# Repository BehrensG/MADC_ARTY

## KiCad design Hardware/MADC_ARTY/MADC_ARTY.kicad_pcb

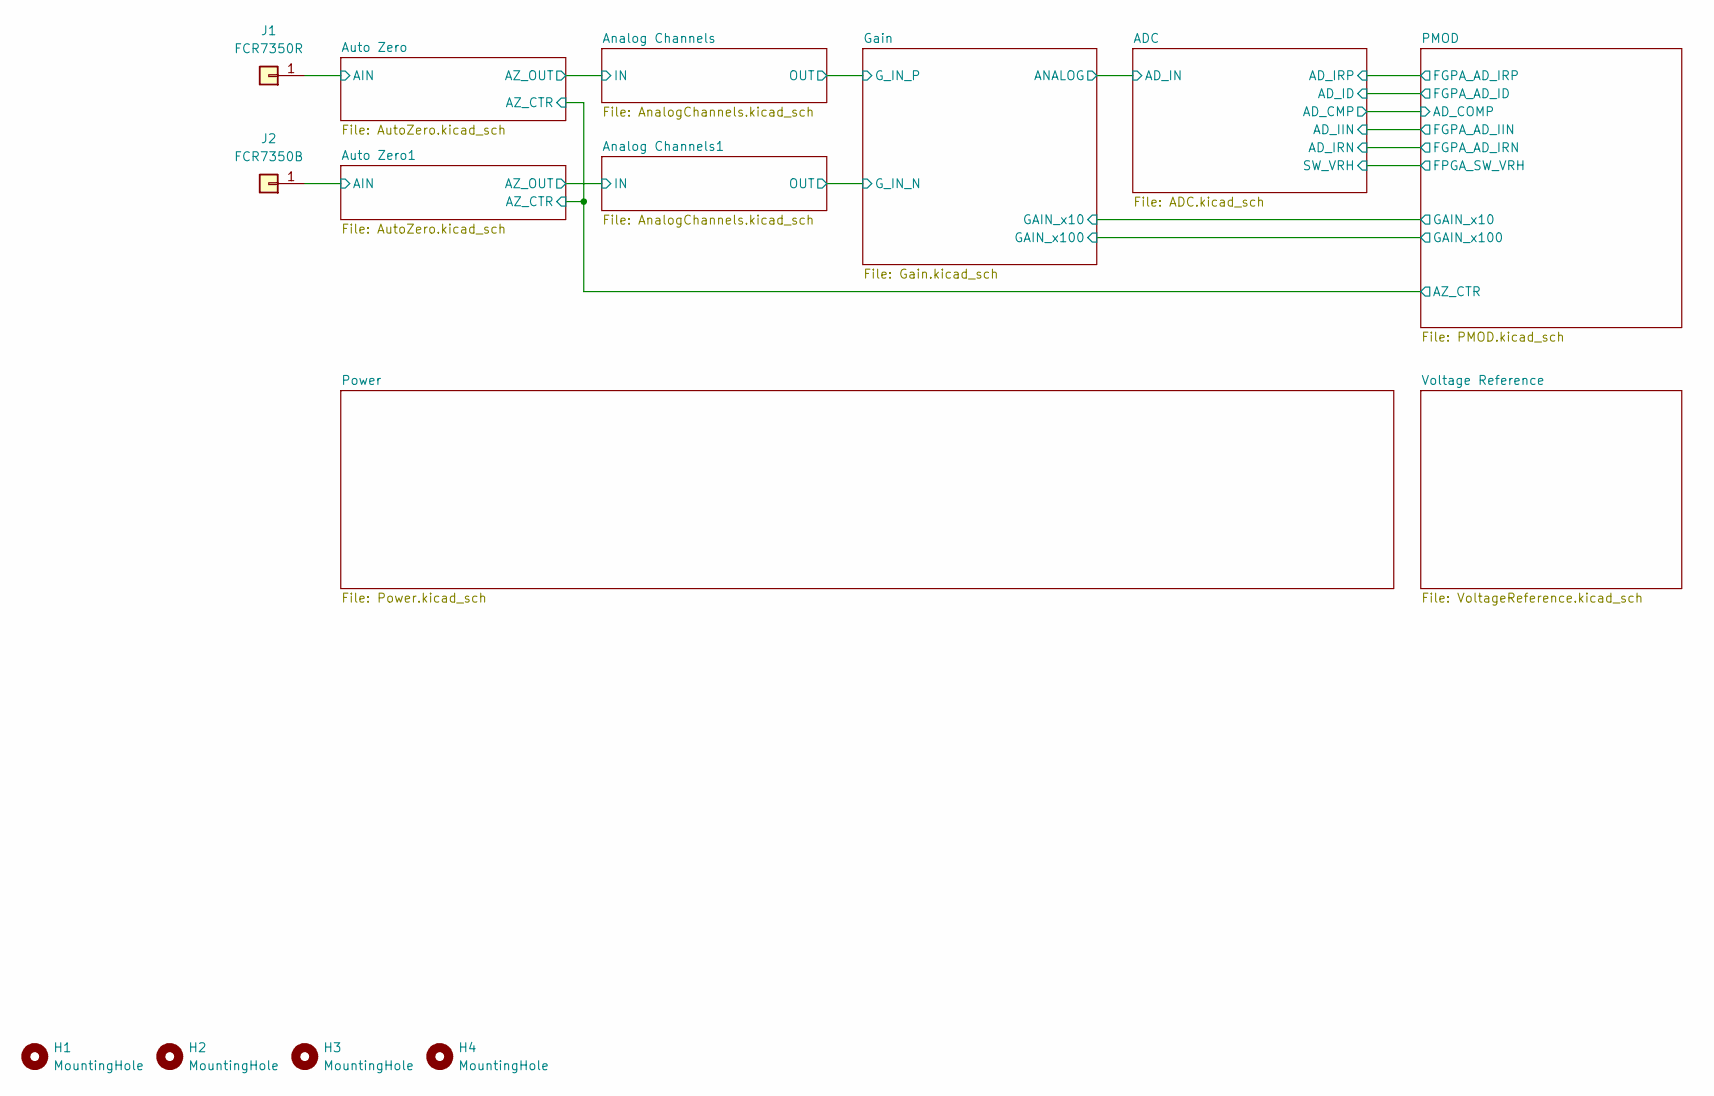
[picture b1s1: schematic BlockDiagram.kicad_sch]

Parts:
H1, H2, H3, H4: MountingHole; MountingHole_3.2mm_M3_DIN965_Pad
J1: FCR7350R; S16N-PC
J2: FCR7350B; S16N-PC

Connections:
/Block Diagram/Auto Zero1/AIN: J2.1; also elsewhere on the board
/Block Diagram/Auto Zero/AIN: J1.1; also elsewhere on the board

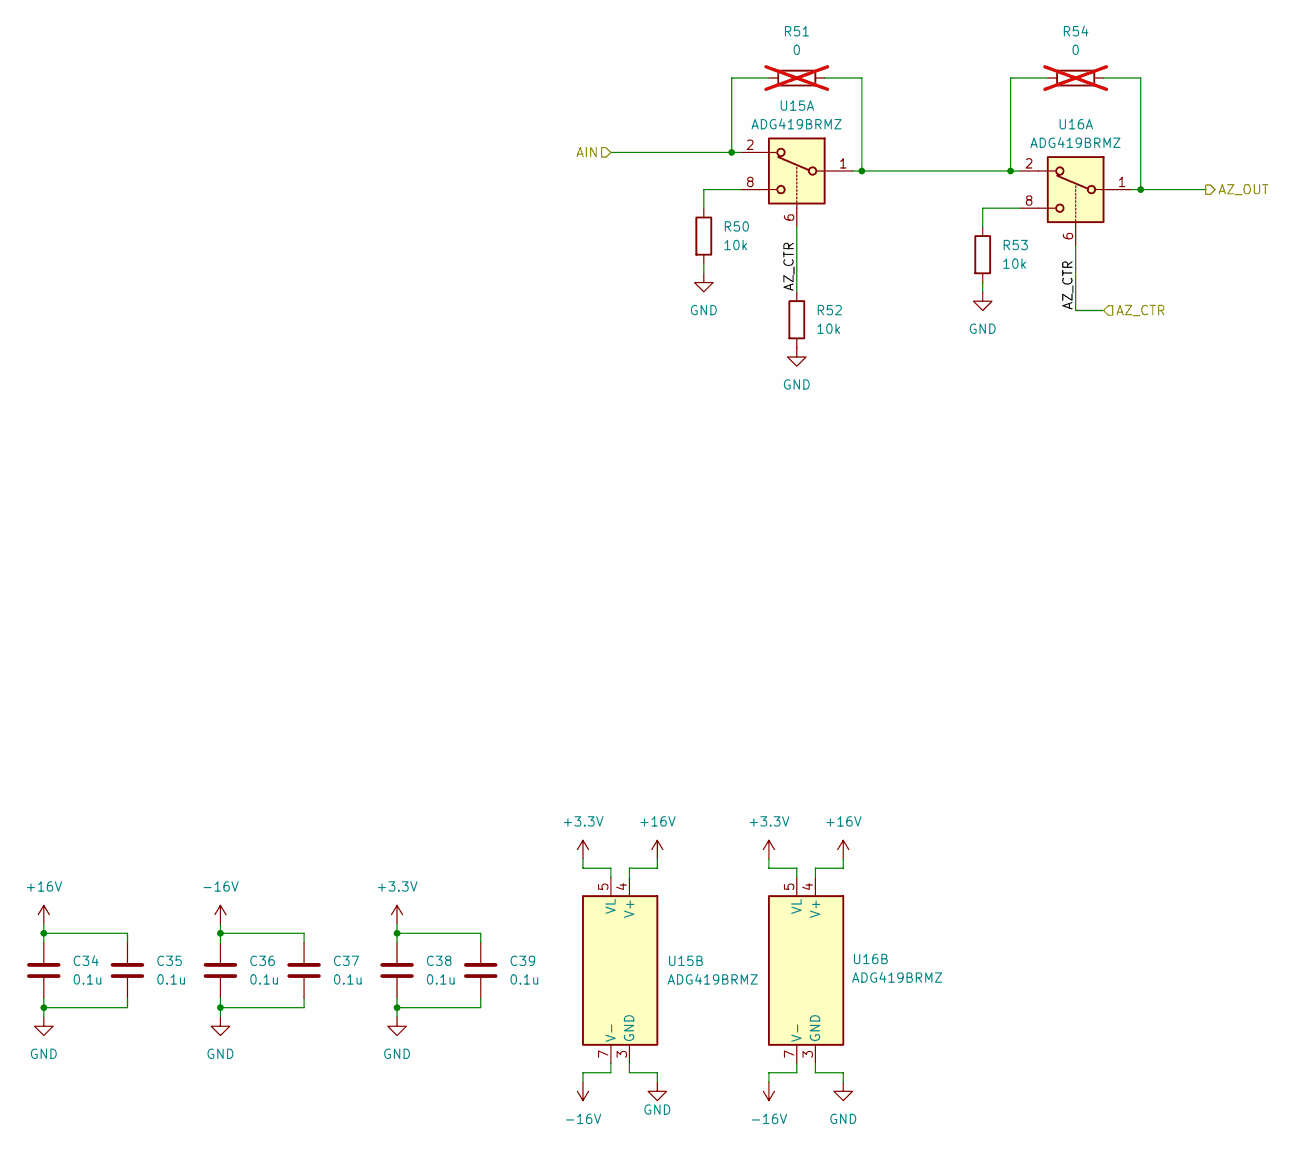
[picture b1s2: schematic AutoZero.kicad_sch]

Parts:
C34, C35, C36, C37, C38, C39: 0.1u; C_0603_1608Metric
R50, R52, R53: 10k; R_0603_1608Metric
R51, R54: 0; R_0603_1608Metric; not fitted
U15, U16: ADG419BRMZ; MSOP-8_3x3mm_P0.65mm

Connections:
+3.3V: C38.1, C39.1, U15.5 (VL), U16.5 (VL); also elsewhere on the board
+16V: C34.1, C35.1, U15.4 (V+), U16.4 (V+); also elsewhere on the board
-16V: C36.1, C37.1, U15.7 (V-), U16.7 (V-); also elsewhere on the board
/Block Diagram/Analog Channels/IN: R54.2, U16.1; also elsewhere on the board
/Block Diagram/Auto Zero/AIN: R51.1, U15.2; also elsewhere on the board
/Block Diagram/Auto Zero/AZ_CTR: R52.1, U15.6, U16.6; also elsewhere on the board
GND: C34.2, C35.2, C36.2, C37.2, C38.2, C39.2, R50.2, R52.2, R53.2, U15.3 (GND), U16.3 (GND); also elsewhere on the board
unnamed: R50.1, U15.8
unnamed: R51.2, R54.1, U15.1, U16.2
unnamed: R53.1, U16.8

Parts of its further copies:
C47, C48, C49, C50, C51, C52: 0.1u; C_0603_1608Metric
R76, R78, R79: 10k; R_0603_1608Metric
R77, R80: 0; R_0603_1608Metric; not fitted
U23, U24: ADG419BRMZ; MSOP-8_3x3mm_P0.65mm

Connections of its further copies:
+3.3V: C51.1, C52.1, U23.5 (VL), U24.5 (VL); also elsewhere on the board
+16V: C47.1, C48.1, U23.4 (V+), U24.4 (V+); also elsewhere on the board
-16V: C49.1, C50.1, U23.7 (V-), U24.7 (V-); also elsewhere on the board
/Block Diagram/Analog Channels1/IN: R80.2, U24.1; also elsewhere on the board
/Block Diagram/Auto Zero1/AIN: R77.1, U23.2; also elsewhere on the board
/Block Diagram/Auto Zero/AZ_CTR: R78.1, U23.6, U24.6; also elsewhere on the board
GND: C47.2, C48.2, C49.2, C50.2, C51.2, C52.2, R76.2, R78.2, R79.2, U23.3 (GND), U24.3 (GND); also elsewhere on the board
unnamed: R76.1, U23.8
unnamed: R77.2, R80.1, U23.1, U24.2
unnamed: R79.1, U24.8

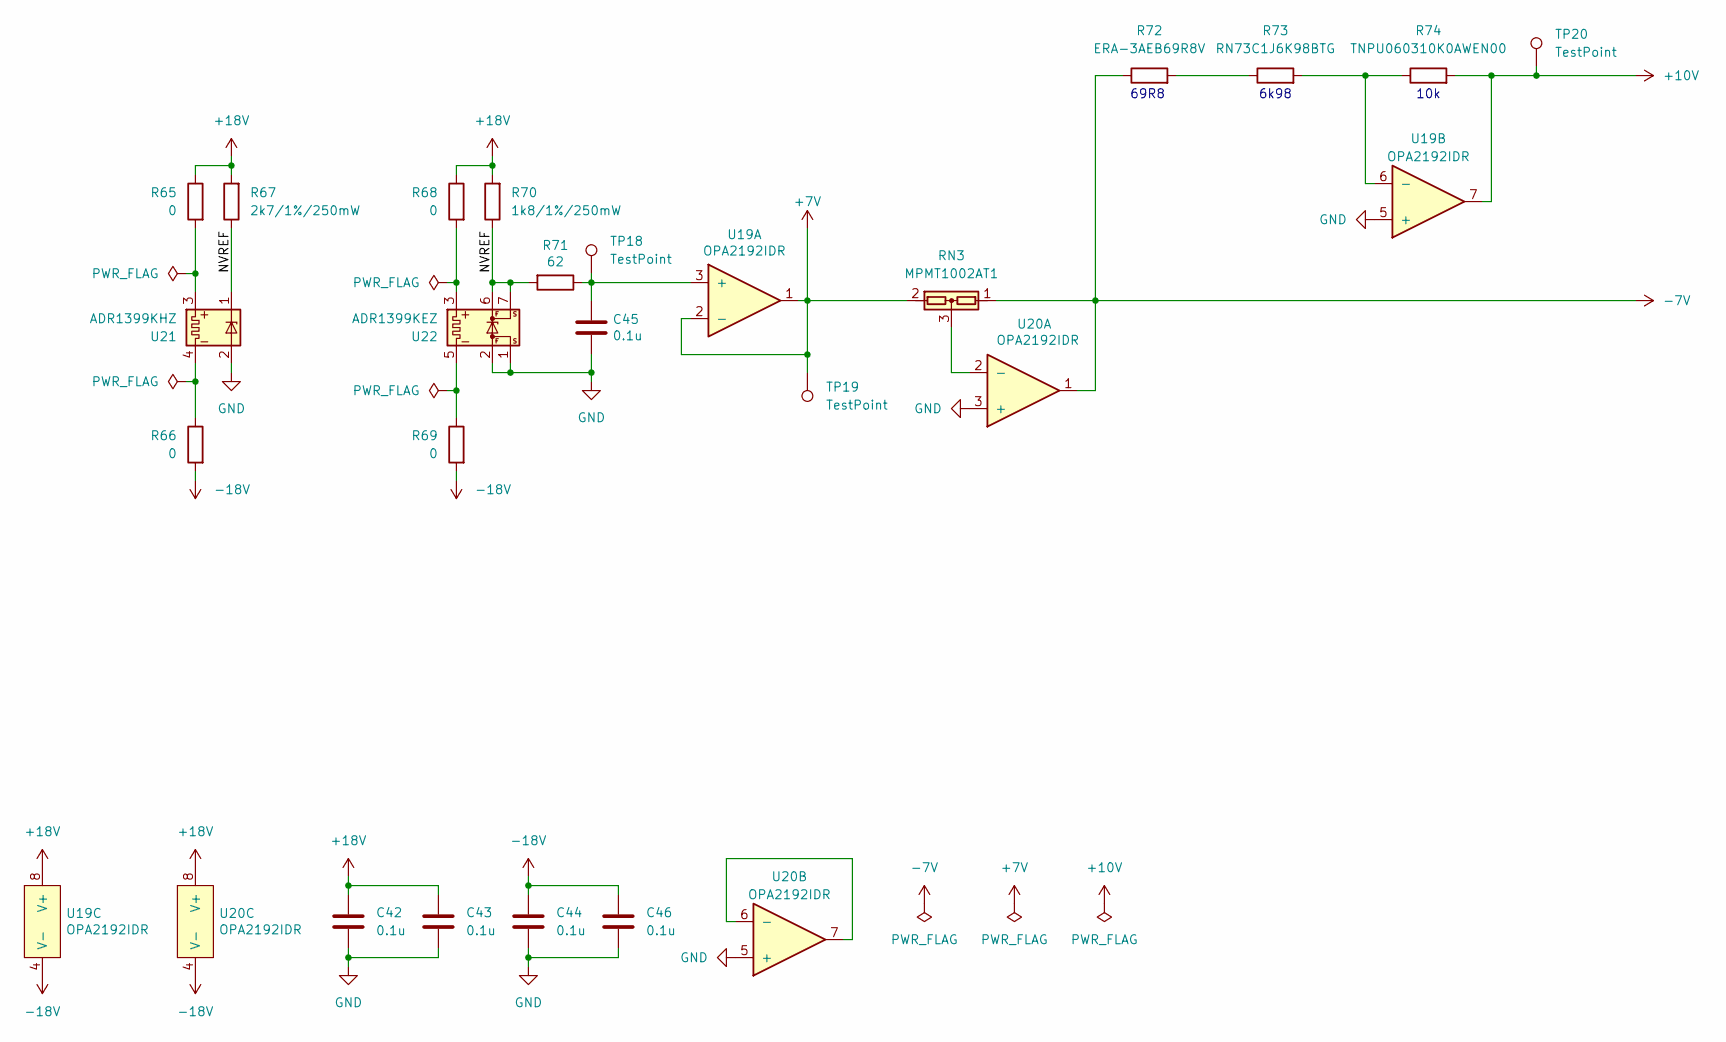
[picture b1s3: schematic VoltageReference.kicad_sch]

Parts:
C42, C43, C44, C45, C46: 0.1u; C_0603_1608Metric
R65, R66, R68, R69: 0; R_0603_1608Metric
R67: 2k7/1%/250mW; R_0603_1608Metric
R70: 1k8/1%/250mW; R_0603_1608Metric
R71: 62; R_0603_1608Metric
R72: ERA-3AEB69R8V; R_0603_1608Metric
R73: RN73C1J6K98BTG; R_0603_1608Metric
R74: TNPU060310K0AWEN00; R_0603_1608Metric
RN3: MPMT1002AT1; SOT-23
TP18, TP19, TP20: TestPoint; TestPoint_Pad_D2.0mm
U19, U20: OPA2192IDR; SOIC-8_3.9x4.9mm_P1.27mm
U21: ADR1399KHZ; Analog_TO-46-4_ThermalShield
U22: ADR1399KEZ; Analog_LCC-8_5x5mm_P1.27mm

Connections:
+7V: RN3.2, TP19.1, U19.1, U19.2 (-); also elsewhere on the board
+10V: R74.2, TP20.1, U19.7; also elsewhere on the board
+18V: C42.1, C43.1, R65.1, R67.2, R68.1, R70.2, U19.8 (V+), U20.8 (V+); also elsewhere on the board
-7V: R72.1, RN3.1, U20.1; also elsewhere on the board
-18V: C44.1, C46.1, R66.2, R69.2, U19.4 (V-), U20.4 (V-); also elsewhere on the board
/Block Diagram/Voltage Reference/NVREF: R67.1, R70.1, R71.2, U21.1, U22.6 (+REFF), U22.7 (+REFS)
GND: C42.2, C43.2, C44.2, C45.2, C46.2, U19.5 (+), U20.3 (+), U20.5 (+), U21.2, U22.1 (-REFS), U22.2 (-REFF); also elsewhere on the board
unnamed: R65.2, U21.3
unnamed: R66.1, U21.4
unnamed: R72.2, R73.1
unnamed: C45.1, R71.1, TP18.1, U19.3 (+)
unnamed: R73.2, R74.1, U19.6 (-)
unnamed: RN3.3, U20.2 (-)
unnamed: U20.6 (-), U20.7
unnamed: R68.2, U22.3 (HEATER+)
unnamed: R69.1, U22.5 (HEATER-)

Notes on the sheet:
6k98
10k
69R8

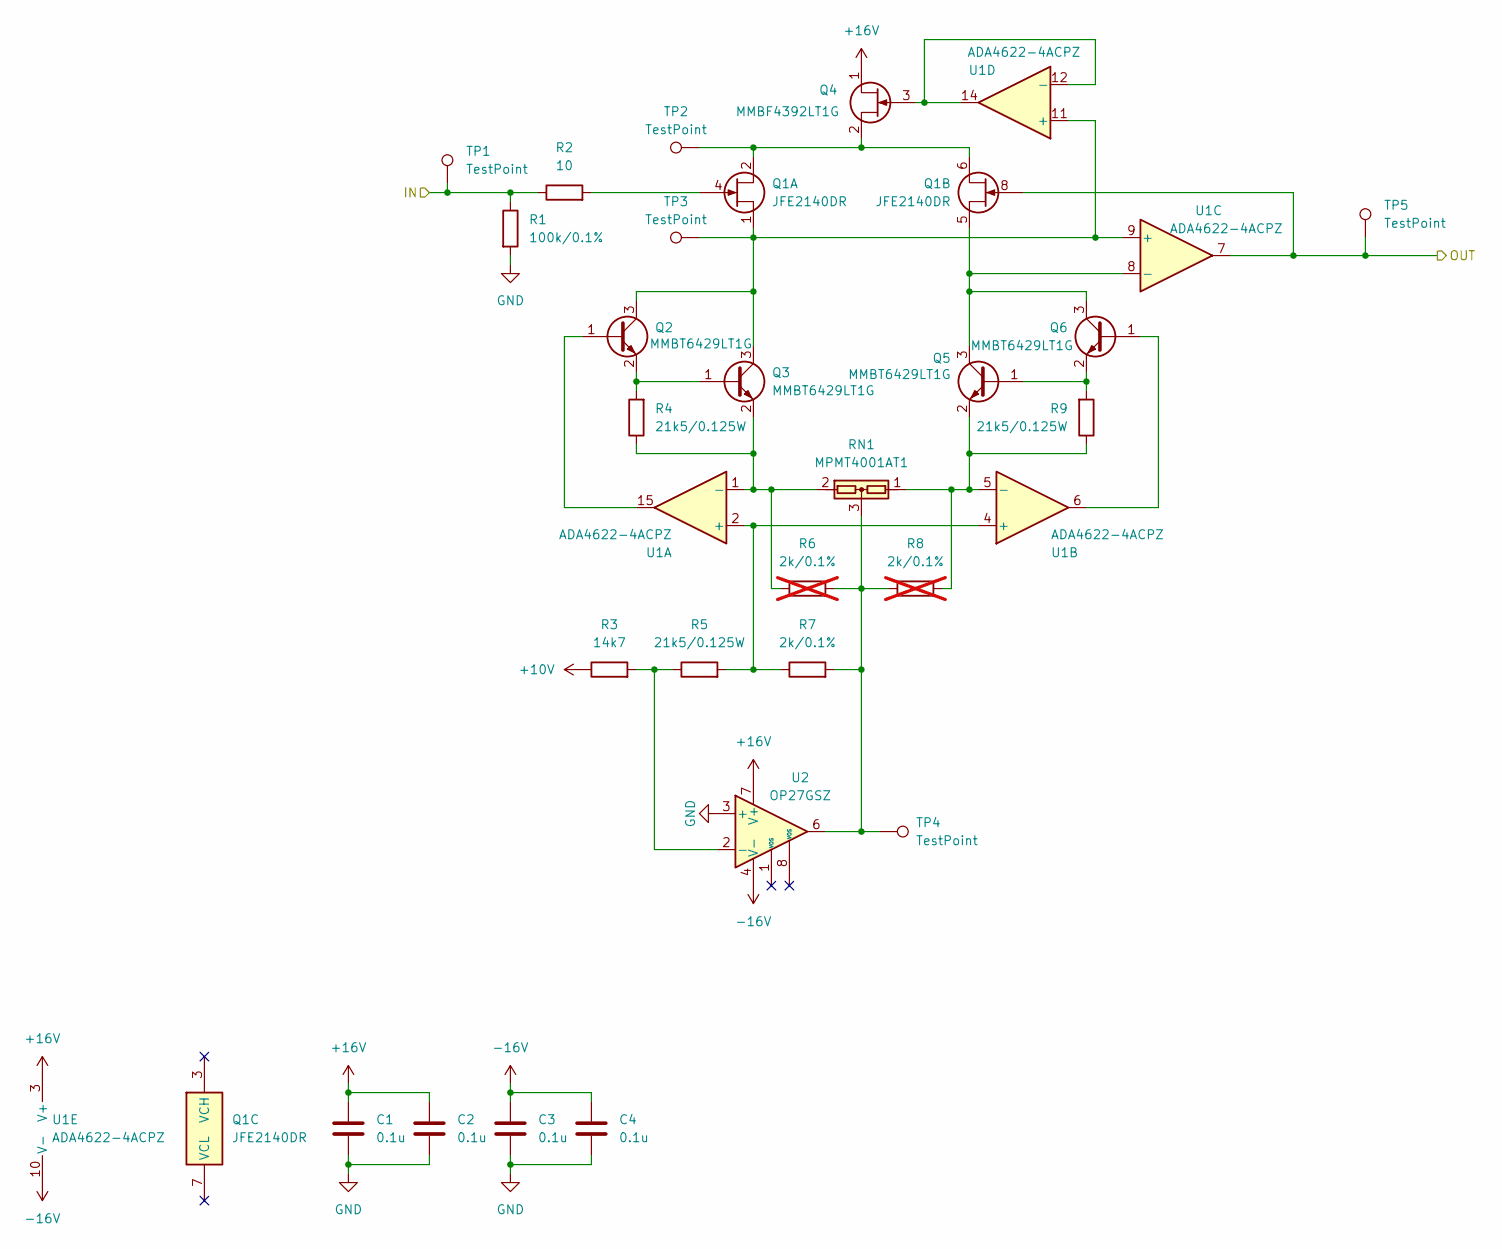
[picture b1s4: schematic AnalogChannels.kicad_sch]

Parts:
C1, C2, C3, C4: 0.1u; C_0603_1608Metric
Q1: JFE2140DR; SOIC-8_3.9x4.9mm_P1.27mm
Q2, Q3, Q5, Q6: MMBT6429LT1G; SOT-23
Q4: MMBF4392LT1G; SOT-23
R1: 100k/0.1%; R_0603_1608Metric
R2: 10; R_0603_1608Metric
R3: 14k7; R_0603_1608Metric
R4, R5, R9: 21k5/0.125W; R_0603_1608Metric
R6, R8: 2k/0.1%; R_0603_1608Metric; not fitted
R7: 2k/0.1%; R_0603_1608Metric
RN1: MPMT4001AT1; SOT-23
TP1, TP2, TP3, TP4, TP5: TestPoint; TestPoint_Pad_D2.0mm
U1: ADA4622-4ACPZ; Analog_LFCSP-16-1EP_4x4mm_P0.65mm_EP2.35x2.35mm
U2: OP27GSZ; SOIC-8_3.9x4.9mm_P1.27mm

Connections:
+10V: R3.1; also elsewhere on the board
+16V: C1.1, C2.1, Q4.1 (D), U1.3 (V+), U1.17 (V+), U2.7 (V+); also elsewhere on the board
-16V: C3.1, C4.1, U1.10 (V-), U2.4 (V-); also elsewhere on the board
/Block Diagram/Analog Channels/IN: R1.1, R2.1, TP1.1; also elsewhere on the board
/Block Diagram/Analog Channels/OUT: Q1.8, TP5.1, U1.7; also elsewhere on the board
GND: C1.2, C2.2, C3.2, C4.2, R1.2, U2.3 (+); also elsewhere on the board
unnamed: Q1.4, R2.2
unnamed: Q2.1 (B), U1.15
unnamed: Q1.1, Q2.3 (C), Q3.3 (C), TP3.1, U1.9 (+), U1.11 (+)
unnamed: Q2.2 (E), Q3.1 (B), R4.2
unnamed: Q3.2 (E), R4.1, R6.1, RN1.2, U1.1 (-)
unnamed: Q4.3 (G), U1.12 (-), U1.14
unnamed: Q1.2, Q1.6, Q4.2 (S), TP2.1
unnamed: Q5.1 (B), Q6.2 (E), R9.2
unnamed: Q1.5, Q5.3 (C), Q6.3 (C), U1.8 (-)
unnamed: Q5.2 (E), R8.2, R9.1, RN1.1, U1.5 (-)
unnamed: Q6.1 (B), U1.6
unnamed: R6.2, R7.2, R8.1, RN1.3, TP4.1, U2.6
unnamed: R5.2, R7.1, U1.2 (+), U1.4 (+)
unnamed: R3.2, R5.1, U2.2 (-)

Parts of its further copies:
C53, C54, C55, C56: 0.1u; C_0603_1608Metric
Q9: JFE2140DR; SOIC-8_3.9x4.9mm_P1.27mm
Q10, Q11, Q13, Q14: MMBT6429LT1G; SOT-23
Q12: MMBF4392LT1G; SOT-23
R81: 100k/0.1%; R_0603_1608Metric
R82: 10; R_0603_1608Metric
R83: 14k7; R_0603_1608Metric
R84, R85, R89: 21k5/0.125W; R_0603_1608Metric
R86, R88: 2k/0.1%; R_0603_1608Metric; not fitted
R87: 2k/0.1%; R_0603_1608Metric
RN4: MPMT4001AT1; SOT-23
TP30, TP31, TP32, TP33, TP34: TestPoint; TestPoint_Pad_D2.0mm
U25: ADA4622-4ACPZ; Analog_LFCSP-16-1EP_4x4mm_P0.65mm_EP2.35x2.35mm
U26: OP27GSZ; SOIC-8_3.9x4.9mm_P1.27mm

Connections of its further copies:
+10V: R83.1; also elsewhere on the board
+16V: C53.1, C54.1, Q12.1 (D), U25.3 (V+), U25.17 (V+), U26.7 (V+); also elsewhere on the board
-16V: C55.1, C56.1, U25.10 (V-), U26.4 (V-); also elsewhere on the board
/Block Diagram/Analog Channels1/IN: R81.1, R82.1, TP30.1; also elsewhere on the board
/Block Diagram/Analog Channels1/OUT: Q9.8, TP34.1, U25.7; also elsewhere on the board
GND: C53.2, C54.2, C55.2, C56.2, R81.2, U26.3 (+); also elsewhere on the board
unnamed: Q9.4, R82.2
unnamed: Q10.1 (B), U25.15
unnamed: Q9.1, Q10.3 (C), Q11.3 (C), TP32.1, U25.9 (+), U25.11 (+)
unnamed: Q10.2 (E), Q11.1 (B), R84.2
unnamed: Q11.2 (E), R84.1, R86.1, RN4.2, U25.1 (-)
unnamed: Q12.3 (G), U25.12 (-), U25.14
unnamed: Q9.2, Q9.6, Q12.2 (S), TP31.1
unnamed: Q13.1 (B), Q14.2 (E), R89.2
unnamed: Q9.5, Q13.3 (C), Q14.3 (C), U25.8 (-)
unnamed: Q13.2 (E), R88.2, R89.1, RN4.1, U25.5 (-)
unnamed: Q14.1 (B), U25.6
unnamed: R86.2, R87.2, R88.1, RN4.3, TP33.1, U26.6
unnamed: R85.2, R87.1, U25.2 (+), U25.4 (+)
unnamed: R83.2, R85.1, U26.2 (-)

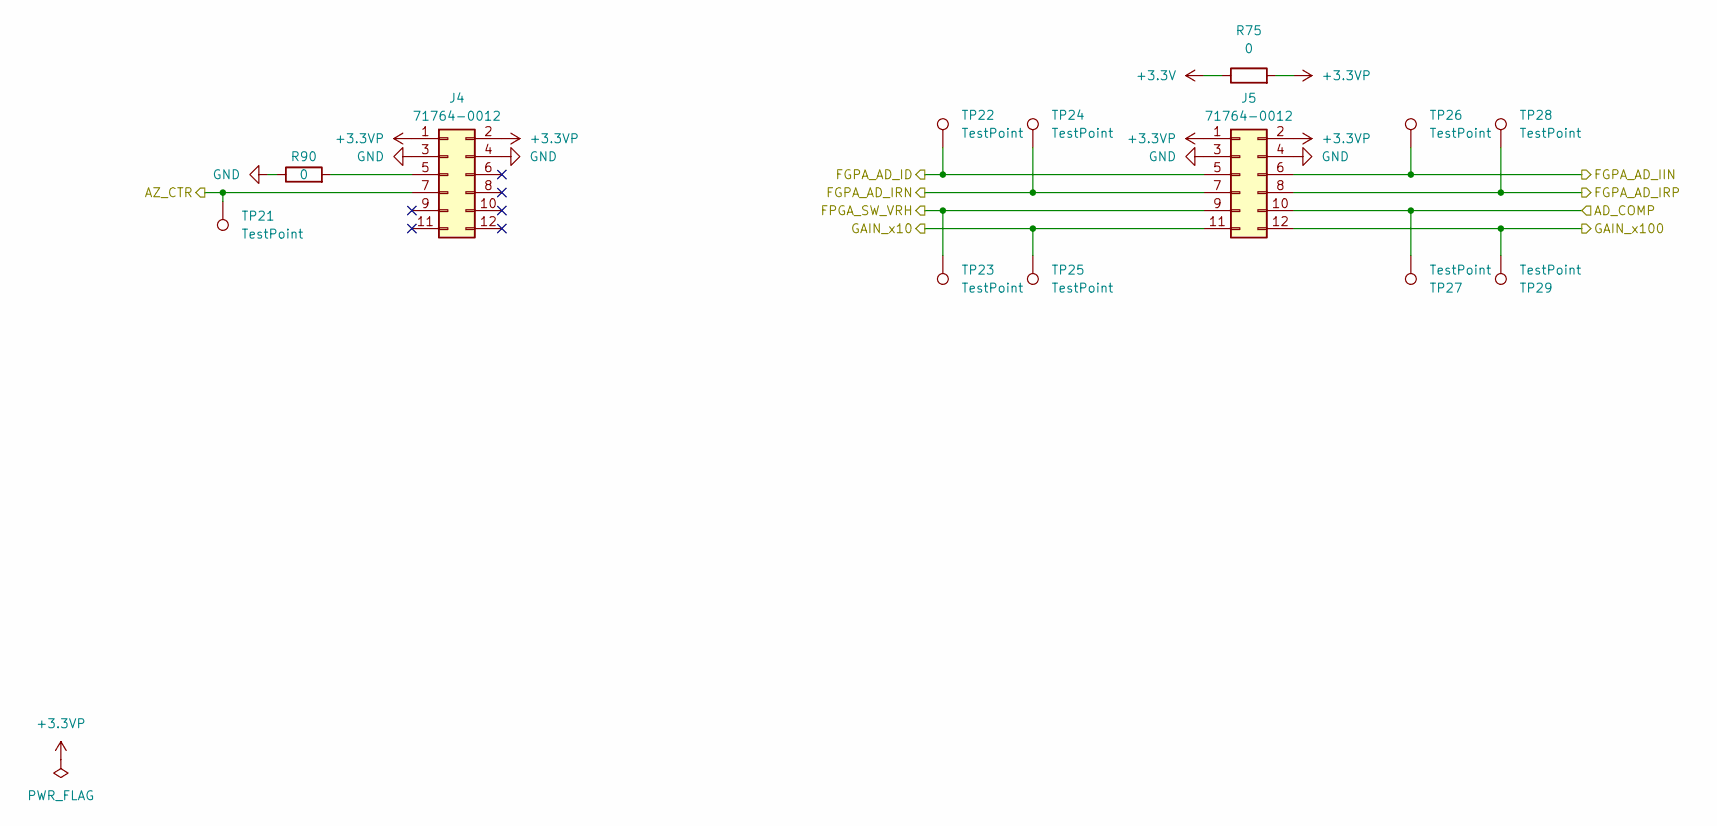
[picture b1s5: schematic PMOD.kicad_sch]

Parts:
J4, J5: 71764-0012; PinHeader_2x06_P2.54mm_Horizontal
R75, R90: 0; R_0603_1608Metric
TP21, TP22, TP23, TP24, TP25, TP26, TP27, TP28, TP29: TestPoint; TestPoint_Pad_D2.0mm

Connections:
+3.3V: R75.1; also elsewhere on the board
+3.3VP: J4.1, J4.2, J5.1, J5.2, R75.2; also elsewhere on the board
/Block Diagram/ADC/AD_CMP: J5.10, TP27.1; also elsewhere on the board
/Block Diagram/ADC/AD_ID: J5.5, TP22.1; also elsewhere on the board
/Block Diagram/ADC/AD_IIN: J5.6, TP26.1; also elsewhere on the board
/Block Diagram/ADC/AD_IRN: J5.7, TP24.1; also elsewhere on the board
/Block Diagram/ADC/AD_IRP: J5.8, TP28.1; also elsewhere on the board
/Block Diagram/ADC/SW_VRH: J5.9, TP23.1; also elsewhere on the board
/Block Diagram/Auto Zero/AZ_CTR: J4.7, TP21.1; also elsewhere on the board
/Block Diagram/Gain/GAIN_x10: J5.11, TP25.1; also elsewhere on the board
/Block Diagram/Gain/GAIN_x100: J5.12, TP29.1; also elsewhere on the board
GND: J4.3, J4.4, J5.3, J5.4, R90.1; also elsewhere on the board
unnamed: J4.5, R90.2

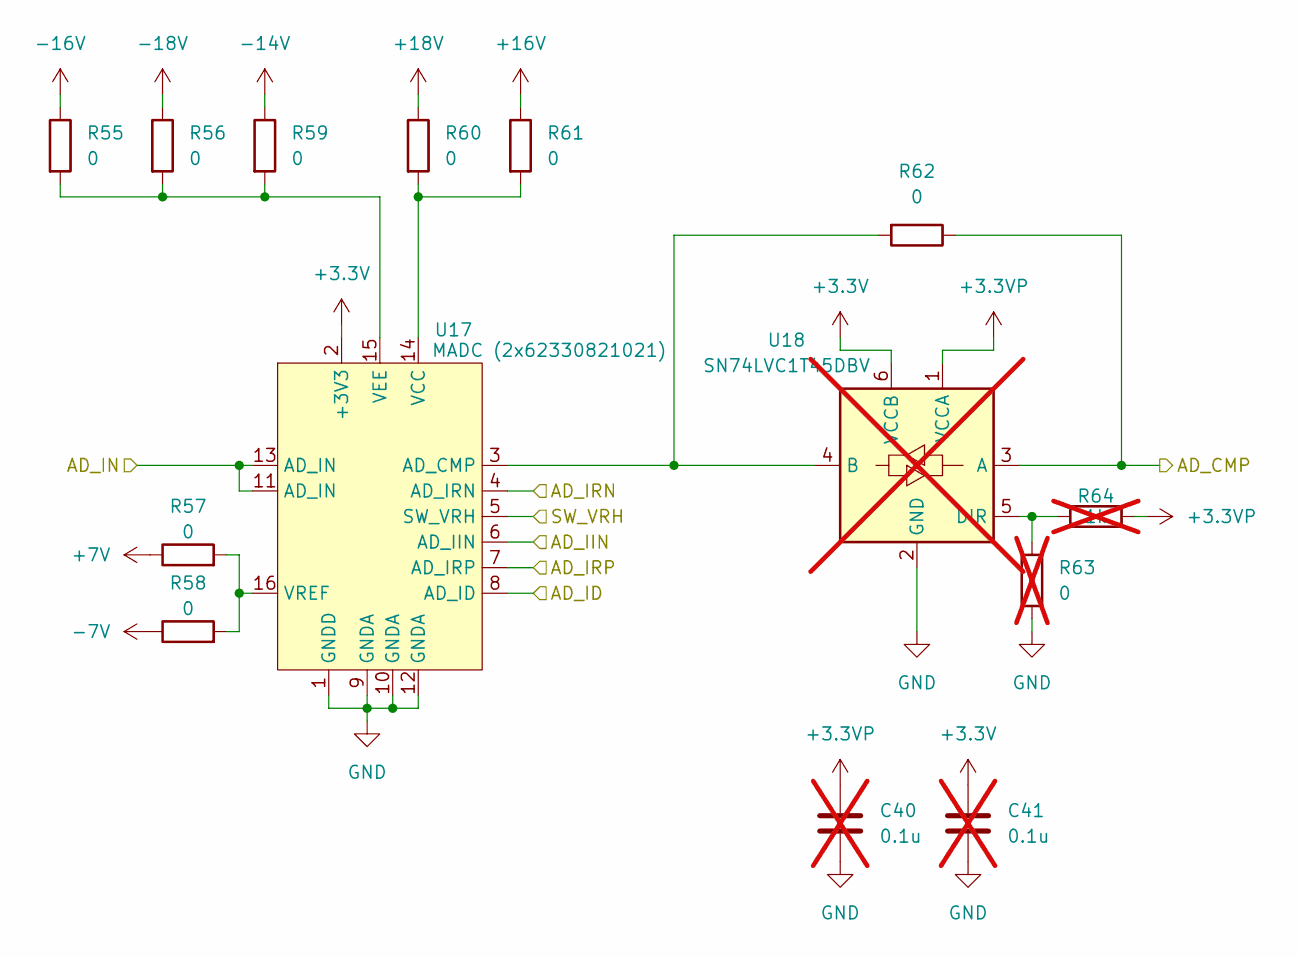
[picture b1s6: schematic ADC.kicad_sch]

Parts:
C40, C41: 0.1u; C_0603_1608Metric; not fitted
R55, R56, R57, R58, R59, R60, R61, R62: 0; R_0603_1608Metric
R63: 0; R_0603_1608Metric; not fitted
R64: 1k; R_0603_1608Metric; not fitted
U17: MADC (2x62330821021); MADC
U18: SN74LVC1T45DBV; SOT-23-6; not fitted

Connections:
+3.3V: C41.1, U17.2 (+3V3), U18.6 (VCCB); also elsewhere on the board
+3.3VP: C40.1, R64.1, U18.1 (VCCA); also elsewhere on the board
+7V: R57.1; also elsewhere on the board
+16V: R61.1; also elsewhere on the board
+18V: R60.1; also elsewhere on the board
-7V: R58.1; also elsewhere on the board
-14V: R59.1; also elsewhere on the board
-16V: R55.1; also elsewhere on the board
-18V: R56.1; also elsewhere on the board
/Block Diagram/ADC/AD_CMP: R62.1, U18.3 (A); also elsewhere on the board
/Block Diagram/ADC/AD_ID: U17.8 (AD_ID); also elsewhere on the board
/Block Diagram/ADC/AD_IIN: U17.6 (AD_IIN); also elsewhere on the board
/Block Diagram/ADC/AD_IN: U17.11 (AD_IN), U17.13 (AD_IN); also elsewhere on the board
/Block Diagram/ADC/AD_IRN: U17.4 (AD_IRN); also elsewhere on the board
/Block Diagram/ADC/AD_IRP: U17.7 (AD_IRP); also elsewhere on the board
/Block Diagram/ADC/SW_VRH: U17.5 (SW_VRH); also elsewhere on the board
GND: C40.2, C41.2, R63.1, U17.1 (GNDD), U17.9 (GNDA), U17.10 (GNDA), U17.12 (GNDA), U18.2 (GND); also elsewhere on the board
unnamed: R62.2, U17.3 (AD_CMP), U18.4 (B)
unnamed: R60.2, R61.2, U17.14 (VCC)
unnamed: R55.2, R56.2, R59.2, U17.15 (VEE)
unnamed: R57.2, R58.2, U17.16 (VREF)
unnamed: R63.2, R64.2, U18.5 (DIR)

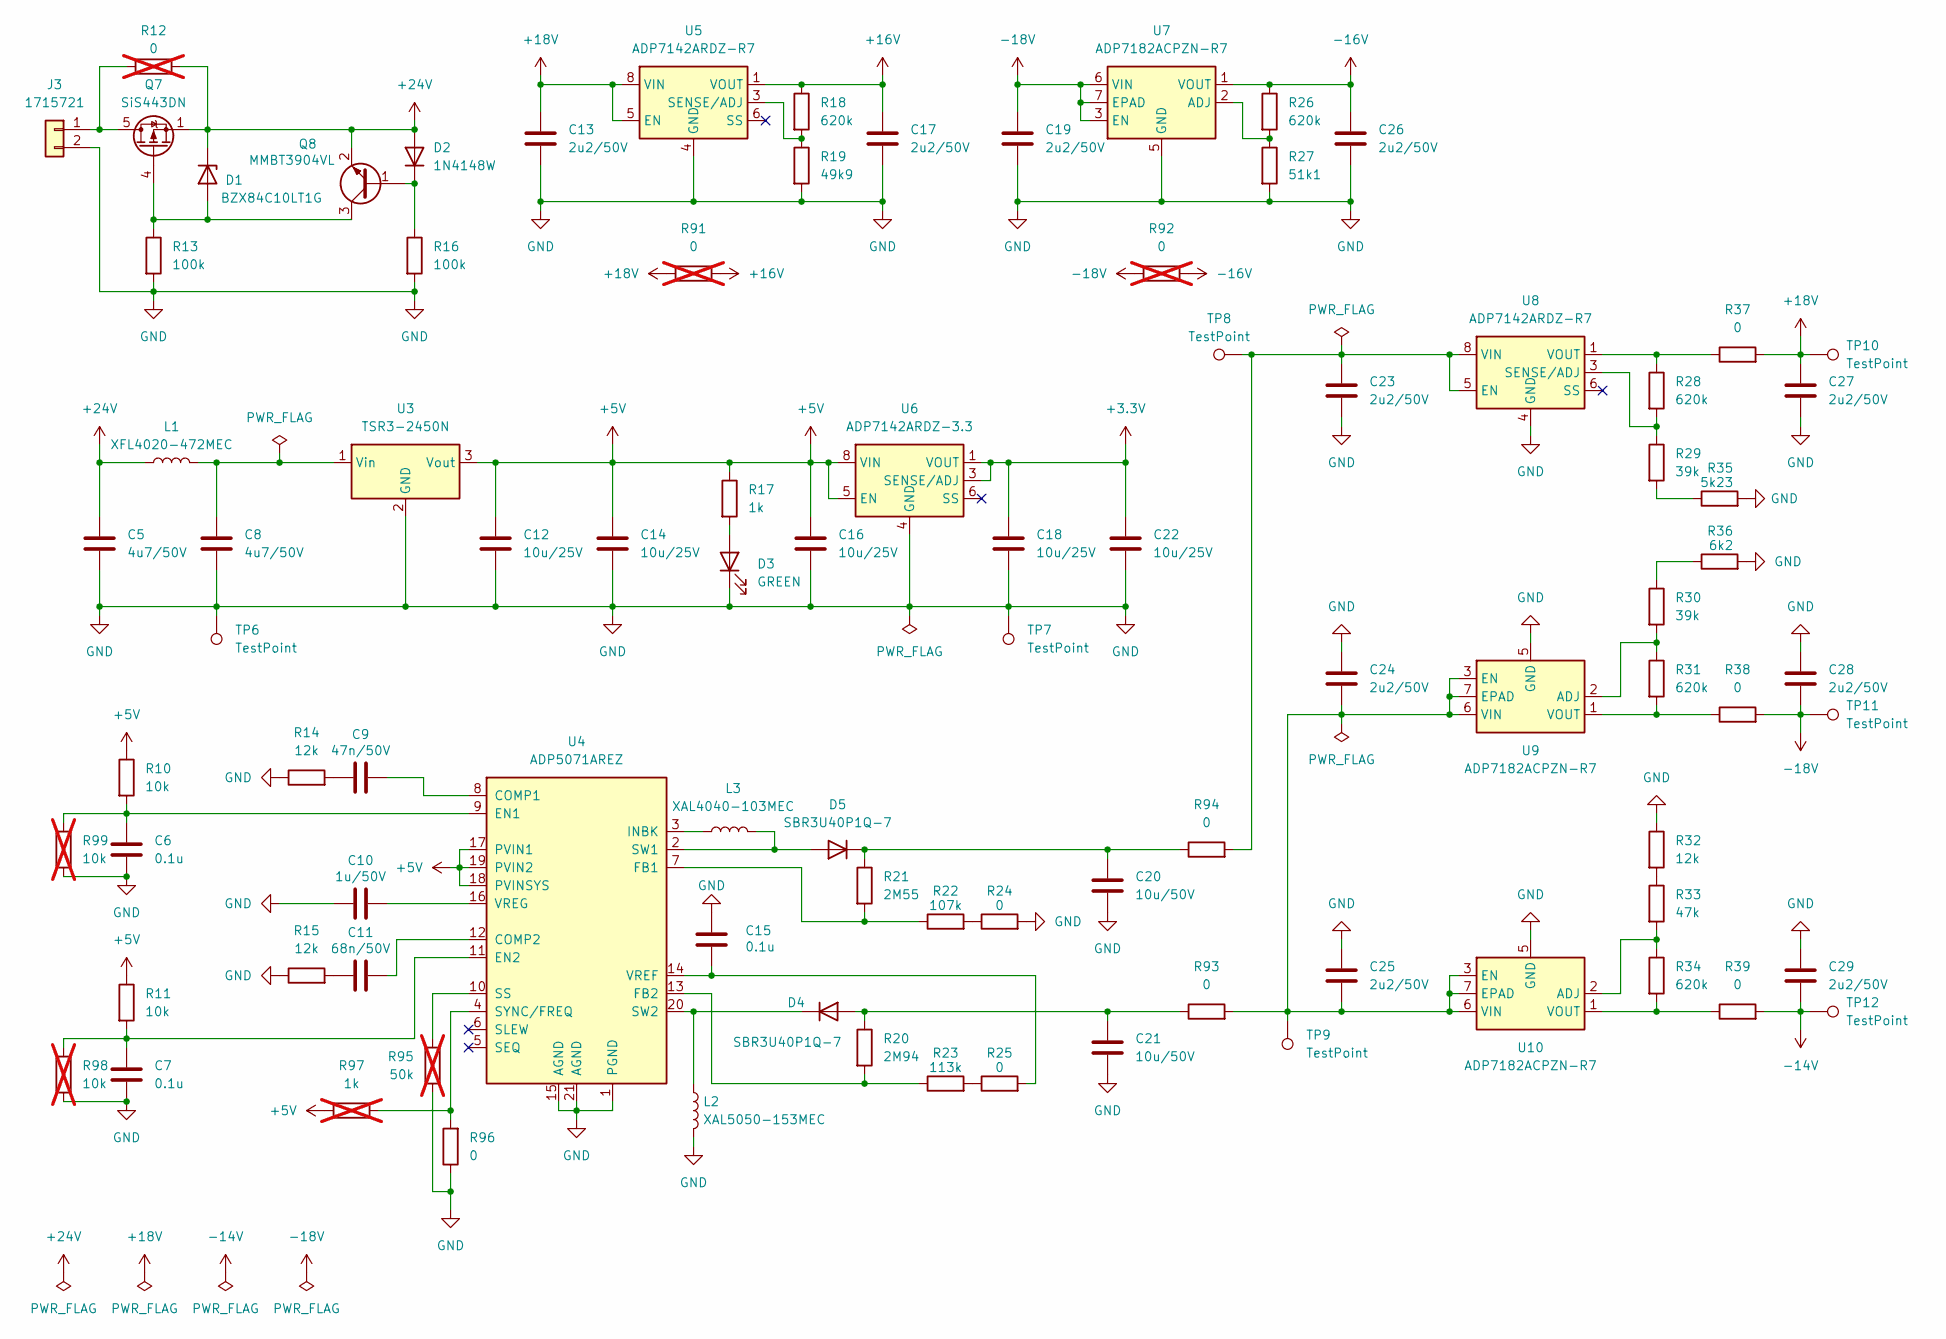
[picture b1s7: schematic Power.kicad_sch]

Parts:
C5, C8: 4u7/50V; C_0805_2012Metric
C6, C7, C15: 0.1u; C_0603_1608Metric
C9: 47n/50V; C_0603_1608Metric
C10: 1u/50V; C_0603_1608Metric
C11: 68n/50V; C_0603_1608Metric
C12, C14, C16, C18, C22: 10u/25V; C_0805_2012Metric
C13, C17, C19, C23, C24, C25, C26, C27, C28, C29: 2u2/50V; C_1206_3216Metric
C20, C21: 10u/50V; C_1206_3216Metric
D1: BZX84C10LT1G; SOT-23
D2: 1N4148W; D_SOD-123
D3: GREEN; LED_0603_1608Metric_Pad1.05x0.95mm_HandSolder
D4, D5: SBR3U40P1Q-7; D_PowerDI-123
J3: 1715721; TerminalBlock_Phoenix_MKDS-1,5-2-5.08_1x02_P5.08mm_Horizont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
L1: XFL4020-472MEC; L_Coilcraft_XAL4020-XXX
L2: XAL5050-153MEC; L_Coilcraft_XAL5050-XXX
L3: XAL4040-103MEC; L_Coilcraft_XAL4040-XXX
Q7: SiS443DN; Vishay_PowerPAK_1212-8_Single
Q8: MMBT3904VL; SOT-23
R10, R11: 10k; R_0603_1608Metric
R12, R91, R92: 0; R_0603_1608Metric; not fitted
R13, R16: 100k; R_0603_1608Metric
R14, R15, R32: 12k; R_0603_1608Metric
R17: 1k; R_0603_1608Metric
R18, R26, R28, R31, R34: 620k; R_0603_1608Metric
R19: 49k9; R_0603_1608Metric
R20: 2M94; R_0603_1608Metric
R21: 2M55; R_0603_1608Metric
R22: 107k; R_0603_1608Metric
R23: 113k; R_0603_1608Metric
R24, R25, R37, R38, R39, R93, R94, R96: 0; R_0603_1608Metric
R27: 51k1; R_0603_1608Metric
R29, R30: 39k; R_0603_1608Metric
R33: 47k; R_0603_1608Metric
R35: 5k23; R_0603_1608Metric
R36: 6k2; R_0603_1608Metric
R95: 50k; R_0603_1608Metric; not fitted
R97: 1k; R_0603_1608Metric; not fitted
R98, R99: 10k; R_0603_1608Metric; not fitted
TP6, TP7: TestPoint; TestPoint_Keystone_5010-5014_Multipurpose
TP8, TP9, TP10, TP11, TP12: TestPoint; TestPoint_Pad_D2.0mm
U3: TSR3-2450N; Converter_DCDC_TRACO_TSR2-24xxN_TSR2-24xxxN_THT
U4: ADP5071AREZ; ETSSOP-20-1EP_4.4x6.5mm_P0.65mm_EP3x4.2mm
U5, U8: ADP7142ARDZ-R7; SOIC-8-1EP_3.9x4.9mm_P1.27mm_EP2.29x3mm
U6: ADP7142ARDZ-3.3; SOIC-8-1EP_3.9x4.9mm_P1.27mm_EP2.29x3mm
U7, U9, U10: ADP7182ACPZN-R7; LFCSP-6-1EP_2x2mm_P0.65mm_EP1x1.6mm

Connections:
+3.3V: C18.1, C22.1, U6.1 (VOUT), U6.2 (VOUT), U6.3 (SENSE/ADJ); also elsewhere on the board
+5V: C12.1, C14.1, C16.1, R10.1, R11.1, R17.1, R97.2, U3.3 (Vout), U4.17 (PVIN1), U4.18 (PVINSYS), U4.19 (PVIN2), U6.5 (EN), U6.7 (VIN), U6.8 (VIN)
+16V: C17.1, R18.1, R91.2, U5.1 (VOUT), U5.2 (VOUT); also elsewhere on the board
+18V: C13.1, C27.1, R37.2, R91.1, TP10.1, U5.5 (EN), U5.7 (VIN), U5.8 (VIN); also elsewhere on the board
+24V: C5.1, D1.3 (K), D2.2 (A), L1.1, Q7.1 (S), Q7.2 (S), Q7.3 (S), Q8.2 (E), R12.2
-14V: C29.2, R39.2, TP12.1; also elsewhere on the board
-16V: C26.1, R26.1, R92.2, U7.1 (VOUT); also elsewhere on the board
-18V: C19.1, C28.2, R38.2, R92.1, TP11.1, U7.3 (EN), U7.6 (VIN), U7.7 (EPAD); also elsewhere on the board
GND: C5.2, C6.2, C7.2, C8.2, C10.1, C12.2, C13.2, C14.2, C15.2, C16.2, C17.2, C18.2, C19.2, C20.2, C21.2, C22.2, C23.2, C24.1, C25.1, C26.2, C27.2, C28.1, C29.1, D3.1 (K), J3.2, L2.2, R13.2, R14.1, R15.1, R16.2, R19.2, R24.2, R27.2, R32.1, R35.2, R36.2, R95.1, R96.1, R98.2, R99.2, TP6.1, TP7.1, U3.2 (GND), U4.1 (PGND), U4.15 (AGND), U4.21 (AGND), U5.4 (GND), U5.9 (GND), U6.4 (GND), U6.9 (GND), U7.5 (GND), U8.4 (GND), U8.9 (GND), U9.5 (GND), U10.5 (GND); also elsewhere on the board
unnamed: C9.1, R14.2
unnamed: C11.1, R15.2
unnamed: D1.1 (A), Q7.4 (G), Q8.3 (C), R13.1
unnamed: D2.1 (K), Q8.1 (B), R16.1
unnamed: D3.2 (A), R17.2
unnamed: C21.1, D4.2 (A), R20.1, R93.1
unnamed: D4.1 (K), L2.1, U4.20 (SW2)
unnamed: D5.2 (A), L3.2, U4.2 (SW1)
unnamed: C20.1, D5.1 (K), R21.1, R94.1
unnamed: J3.1, Q7.5 (D), R12.1
unnamed: R22.2, R24.1
unnamed: R23.2, R25.1
unnamed: R28.1, R37.1, U8.1 (VOUT), U8.2 (VOUT)
unnamed: R29.2, R35.1
unnamed: R30.1, R36.1
unnamed: R32.2, R33.1
unnamed: C8.1, L1.2, U3.1 (Vin)
unnamed: C9.2, U4.8 (COMP1)
unnamed: C11.2, U4.12 (COMP2)
unnamed: C6.1, R10.2, R99.1, U4.9 (EN1)
unnamed: C7.1, R11.2, R98.1, U4.11 (EN2)
unnamed: R21.2, R22.1, U4.7 (FB1)
unnamed: R20.2, R23.1, U4.13 (FB2)
unnamed: L3.1, U4.3 (INBK)
unnamed: R95.2, U4.10 (SS)
unnamed: R96.2, R97.1, U4.4 (SYNC/FREQ)
unnamed: C15.1, R25.2, U4.14 (VREF)
unnamed: C10.2, U4.16 (VREG)
unnamed: R18.2, R19.1, U5.3 (SENSE/ADJ)
unnamed: R26.2, R27.1, U7.2 (ADJ)
unnamed: C23.1, R94.2, TP8.1, U8.5 (EN), U8.7 (VIN), U8.8 (VIN)
unnamed: R28.2, R29.1, U8.3 (SENSE/ADJ)
unnamed: R30.2, R31.1, U9.2 (ADJ)
unnamed: R31.2, R38.1, U9.1 (VOUT)
unnamed: R33.2, R34.1, U10.2 (ADJ)
unnamed: C24.2, C25.2, R93.2, TP9.1, U9.3 (EN), U9.6 (VIN), U9.7 (EPAD), U10.3 (EN), U10.6 (VIN), U10.7 (EPAD)
unnamed: R34.2, R39.1, U10.1 (VOUT)
